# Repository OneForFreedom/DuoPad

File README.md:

# DuoPad
Its a wasd and space in one side and arrow keys in another to play them crappy two player games (basically two identical macropads)

They're both wireless and just plug and play or should i say. Bluetooth connect and play? 

Yea no. They're plug and play. Lipo batteries cost too much.

I made these because i thought to myself why not!

So I made this!

# Eye candy as always!

P.S BEFORE ANYONE TELLS ME THAT THE EXTRA SPACE IS UNNECESSARY. THAT EMPTY SPACE IS WHERE THE BATTERY WILL BE!
# And that juicy BOM!

| Item            | Price (£)  | Price (\$)  | Link                                                                |
| --------------- | ---------- | ----------- | ------------------------------------------------------------------- |
| Switches        | £2.59      | \$3.47      | [AliExpress](https://www.aliexpress.com/item/1005006578935785.html) |
| Rotary Encoder  | £1.91      | \$2.56      | [AliExpress](https://www.aliexpress.com/item/1005005983134515.html) |
| Encoder Knobs   | £1.07      | \$1.43      | [AliExpress](https://www.aliexpress.com/item/1005005983134515.html) |
| nice!nano v2 ×2 | £4.66      | \$6.25      | [AliExpress](https://www.aliexpress.com/item/1005001621678794.html) |
| Keycaps 1 ×2    | £1.92      | \$2.57      | [AliExpress](https://www.aliexpress.com/item/1005006904507329.html) |
| Keycaps 2 ×2    | £6.86      | \$9.19      | [AliExpress](https://www.aliexpress.com/item/1005006005905021.html) |
| Cables ×2       | £1.22      | \$1.63      | [AliExpress](https://www.aliexpress.com/item/33014968983.html)      |
| PCB             | £13.52     | \$18.10     | N/A                                                                 |
| Parcels (Royal mail)  | £3.35      | \$4.49      | N/A                                                                 |
| **Total**       | **£37.06** | **\$49.69** | —                                                                   |

 Budget doesn't allow for battery. Hopefully I can save up to buy one*

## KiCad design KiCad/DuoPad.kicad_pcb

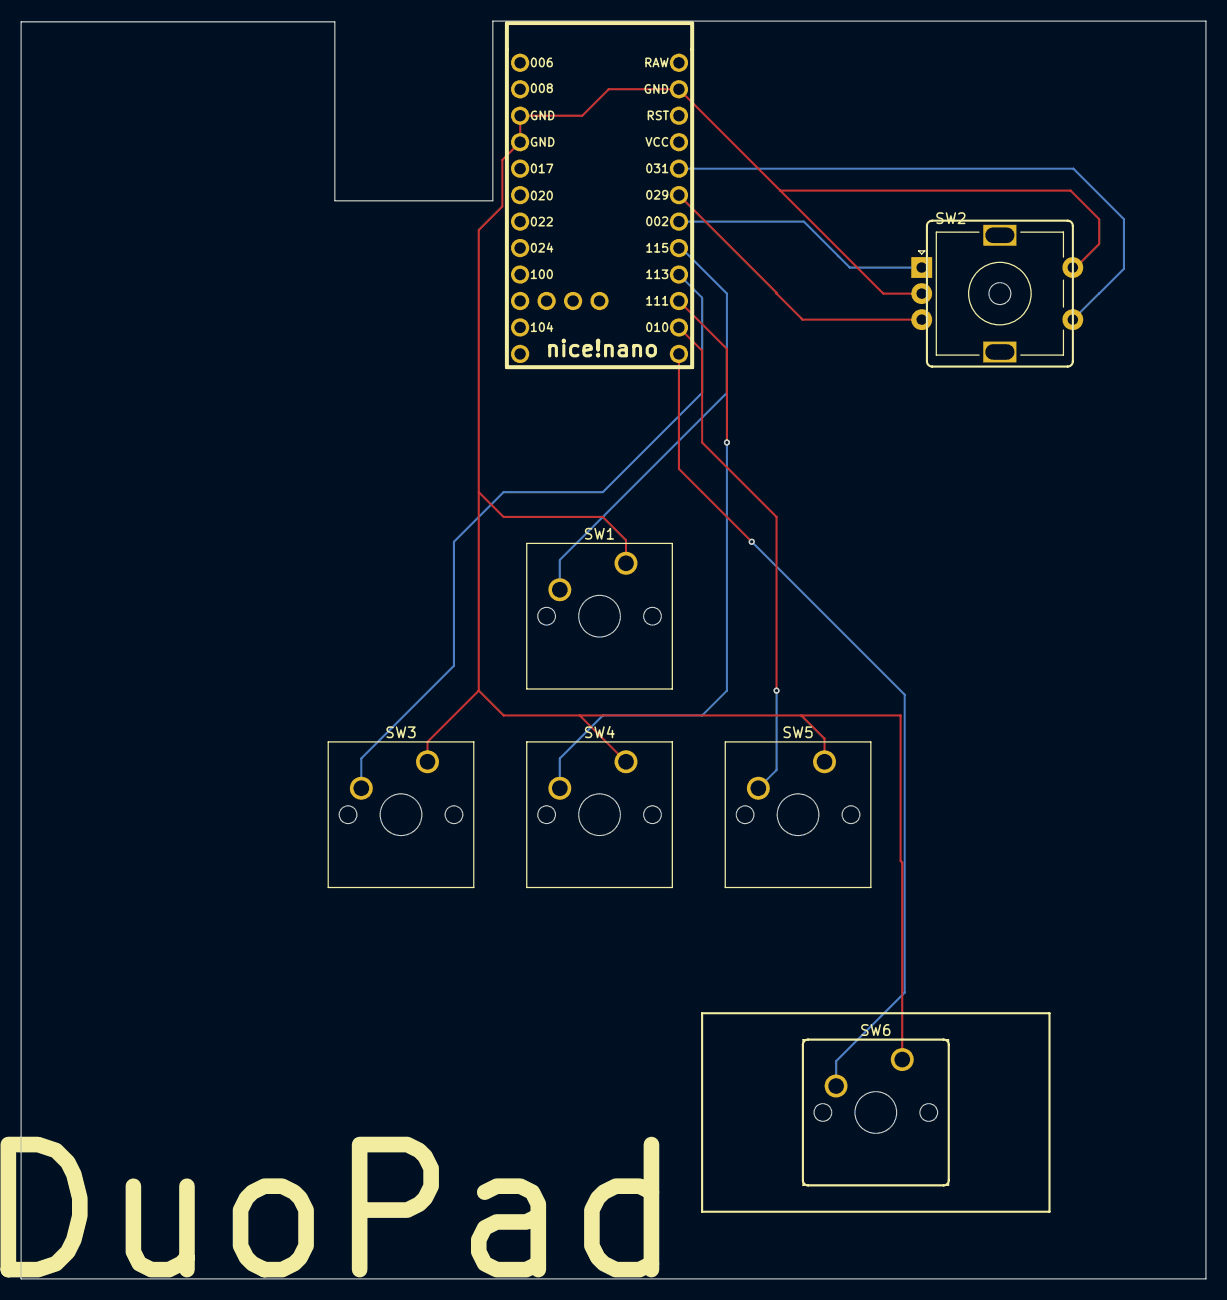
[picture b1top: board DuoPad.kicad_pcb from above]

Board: 2 copper layers, 113.7 x 120.7 mm, 7 parts (0 on the bottom side), 9 nets.

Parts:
SW1, SW3, SW4, SW5, SW6: SW_Push; SW_Cherry_MX_1.00u_PCB
SW2: RotaryEncoder_Switch; RotaryEncoder_Alps_EC11E-Switch_Vertical_H20mm_MountingHoles
U1: nice_nano

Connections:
AIN0/P0.02: SW2.A, U1.18 (AIN0/P0.02)
AIN5/P0.29: SW2.B, U1.19 (AIN5/P0.29)
AIN7/P0.31: SW2.S1, U1.20 (AIN7/P0.31)
GND: SW1.1, SW2.C, SW2.S2, SW3.1, SW4.1, SW5.1, SW6.1, U1.3 (GND), U1.4 (GND), U1.23 (GND)
NFC1/P0.09: SW6.2, U1.13 (NFC1/P0.09)
NFC2/P0.10: SW5.2, U1.14 (NFC2/P0.10)
P1.11: SW4.2, U1.15 (P1.11)
P1.13: SW3.2, U1.16 (P1.13)
P1.15: SW1.2, U1.17 (P1.15)

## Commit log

2025-07-16 Rename DuoPad.kicad_pro to KiCad/DuoPad.kicad_pro
2025-07-16 Rename DuoPad NBG.png to Images/DuoPad NBG.png
2025-07-16 Rename DuoPad.zip to Production/DuoPad.zip
